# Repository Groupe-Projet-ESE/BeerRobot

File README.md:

# <div align="center">BeerRobot</div> 
__Last update of README__ : 23/01/2023

## Introduction
Elèves en option ESE (Electronique et Systèmes Embarqués) au sein de l'ENSEA (Ecole Nationale Supérieures de l'Electronique et de ses Applications), réalisant un robot comme projet central de leur option.  

## Objectifs du projet
Le but du projet est de créer un robot permettant d'attraper des canettes, de relever la couleur de cette dernière, se déplacer avec la canette attrapée et la déposer dans la zone adaptée selon sa couleur. Par ailleurs le robot devra se repérer sur une table afin de ne pas tomber.   

## Matériels et composants à notre disposition

__Microcontroleur__ : STM32G070RBT6 (Farnell : 3365377)  
__Quartz 16 MHz__ : (Farnell : 2853935)  
__Connecteur SWD/STLink__ : (Farnell : 3226055)  
__Driver moteur__ : ZXBM5210-S (Farnell : 3935372)   
__Moteurs__ : DfRobot FIT0520 ou FIT0521   
__Régulateur 5V__ : AZ1117CH2-5.0TRG1 (Farnell : 3942512)  
__Régulateur 3.3V__ : MIC5317-3.3YM5 (Farnell : 2920683)  
__Batterie NIMH 7.2V 1.3Ah__ (RS : 777-0377)    
__Capteur bordure__ : Sharp GP2Y0D805Z0F (Generationrobots : A-000000-00046)   
__Capteur TOF__ : VL53L0X (Generationrobots : A-000000-03233)   
__Capteur de couleur__ : VEML3328 (Farnell : 3517203)  
__Servomoteur__ : XL320 (Generationrobots : A-000000-01282)  
Connecteurs JST 2.54mm  

## Membres du groupe et rôles
Le groupe de projet est constitué de 4 membres, chacun ayant divers responsabilités.  
- __Chelsea COMLAN__ : responsable Hardware
- __Loïcia KOEHL__ : responsable intégration
- __Quentin SIMON__ : responsable Software
- __Alix HAVRET__ : responsable livrables

__Encadrants du projet__ : Mr Fiack , Mr Tauvel  
__Intervenants extérieur__ : Mme Quittel, Mr Jauffrey, Mr Le Bidan  

### Contenus des dossiers
La démonstration finale se trouve sur la master. 

#### Additional documents
Contient l'ensemble des images necessaire à la rédaction de ce README, le rapport de mi-projet rédigé en novembre ainsi que le diaporama de notre présentation du robot en décembre.   

  #### Hardware
Contient le projet Kicad avec l'ensemble des fichiers electronique ainsi que le fichier de routage du PCB.  
Le PCB a été produit à l'extérieur de l'ENSEA.  

  #### Software 
Contient les codes "annexes", c'est à dire les codes des composants testé sur le STM32F746NG.  
Le projet CubeIDE a destination de la STM32G0 (notre microcontroleur de projet) se trouve sur la master. 

  #### 3D 
  Contient certains fichiers 3D pour la réalisation du robot

## Architecture générale du projet

Au debut du projet nous avons eu la liste de l'ensemble des composants auxquels nous avions accès pour la réalisation du robot et afin de remplir ses divers fonctionnalités.   
Le schéma architectural au début du projet nous a permit de définir l'ensemble des entrées necessaires dans notre microcontroleur et les divers flux de données qui allaient entrer en jeu.  

### Rôles et utilité des divers composants, capteurs 
#### Moteurs FIT501
Deux Moteurs à courant continu, alimenté en xx V, permettant de faire tourner 2 roues. Le moteur a également un encodeur.  

### Servomoteur XL320
Servomoteur qui permettra de faire bouger la pince necessaire pour saisir les canettes.

### Capteur couleur TCS3200
Capteur permettant de detecter la couleur de la canette à l'aide de filtres superposés à des LEDS.

### Capteur de bordure 
Capteur infra-rouge qui détecte si il y a un object en face de lui.

### Capteur TOF 
Time Of Flight, renvoie le temps qu'a prit la source lumineuse du capteur pour rebondir sur un object et revenir. Cela nous permet d'avoir notre distance par rapport à un objet. (en mm)

## 3D du robot 
Nous avons prit la décision de modifier le design initial du robot sur onshape.  
Ajout d'un roulement en plus à l'avant, modification de l'emplacement de la pince et la forme de celle ci. Une fois le PCB reçu, des modifications ont été effectuées afin de permettre un bon placement de l'ensemble des fils.  
Par ailleurs nous avons aménagés divers emplacements pour les différents capteurs : couleurs, bordure et distance. 

## Hardware 
### Schema electrique
A partir du schema architectural réalisé au début du projet, nous avons commencé le schéma électrique du projet sur Kicad.  
Ce dernier a été séparé en plusieurs feuilles afin de pouvoir organiser les différentes partie : STM32, alimentation, capteurs, moteurs, servomoteur.

### PCB
__09/11/2022__ Reception du PCB  
__Soudeurs__ : Loïcia et Chelsea  
L'ensemble des soudures ont été réalisées à la main, lee 25/11/2022  l'ensemble des composants étaient soudés sur la carte.   
Nous avons soudés les connecteurs au fur et à mesure de la réalisation des tests.

## Software

Le code sera utilisé dans diverses tâches (utilisation de FreeRTOS). Chaque état décrit dans le diagramme à états correspondra à une tâche.  
Une tâche pourra faire appel à de la donnée, ou en consommer. Dans chaque tâche nous feront appel à divers bouts de code permettant de démarrer un capteur, un moteur, un servo, etc ...  

Pour effectuer nos tests sur les capteurs, nous avons implémentés un shell. Chacun des capteurs ont été validé sur la STM32F746NG, et ensuite leur code était intégré à la STM32G0.
La shell nous a permit de faire une première démonstration. 

### Moteurs : 
Après les premiers tests, nous avons remarqué que pour une même commande vitesse, les 2 roues ne tournaient pas à la même vitesse, de ce fait le robot n'allait pas droit.  Afin de régler ce problème il était nécessaire de mettre en place un asservissement.
#### Asservissement 
Nous avons décidé de faire un correcteur PI (Proportionnel Intégral).  

**schéma**

Pour cela il nous fallait donc récupérer des informations venant du robot et du microcontroleur :  
-	Valeur vitesse demandée  pour les roues
-	Valeur vitesse réelle des 2 roues (les 2 étant différentes du à la qualité des moteurs)  
-	Nombre de tick moteur  

Ces infos nous permettaient alors de créer le correcteur PI avec :  
-	Coefficient proportionnel Kp  
-	Coefficient intégrateur Ki  

Une fois avoir réussi à récupérer la valeur de la vitesse en entrée et le nombre de tick nous avons pu commencer à coder l’asservissement.  

Pour ce faire il fallait que l’on fasse la différence de valeur entre la valeur actuelle et la valeur précédente de vitesse. Par la suite, nous pouvions calculer l’erreur entre la valeur d’entrée et la vitesse du robot pour voir si il avançait à la vitesse souhaitée.  
Une fois toutes la valeurs et calculs mis en place, nous avons pu commencer la recherche des valeurs pour nos coefficients. Il fallait trouver les valeurs avec lesquelles il y avait le moins d’oscillation possible.  

### Fonctionnement des capteurs 
#### Capteur bordure 

#### Capteur TOF 
Le capteur TOF a un driver déja créé, ce qui nous a permit de réutiliser les fonctions déja existantes permettant l'initialisation du capteur, et la récupération des valeurs .L'activation de la pin GPIO nous permet d'acquérir les valeurs en continue tant que le TOF est actif.   
Lorsque que l'on veut utiliser 2 TOF, c'est la pin XSHUT qui rentre en jeux. Les 2 TOF étant sur le même I2C, on activera uniquement le TOF du capteur que l'on veut utiliser.  

#### Capteur couleurs
Non fonctionnel.

__Objectif de la présentation finale :__

La démo implémentée et téléchargée sur la master permet au robot de faire une première phase de démarrage, de se lancer en mode "recherche" canette. Une fois une canette repérée à une certaine distance, le robot continue sa recherche vers la zone où il a capté une canette. Une fois que la canette est captée dans le creue du robot, alors la pince est déclenchée en mode fermeture.

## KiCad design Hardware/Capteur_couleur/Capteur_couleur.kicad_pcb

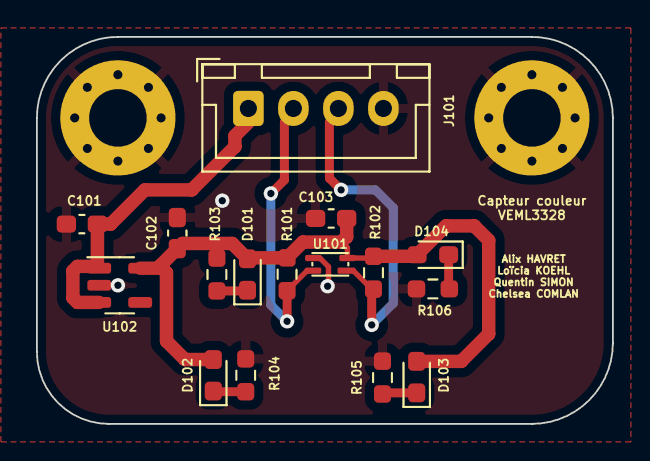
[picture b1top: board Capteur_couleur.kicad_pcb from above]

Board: 2 copper layers, 32.0 x 21.5 mm, 18 parts (0 on the bottom side), 9 nets.

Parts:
C101, C102: 1uF; C_0603_1608Metric_Pad1.08x0.95mm_HandSolder
C103: 100n; C_0603_1608Metric_Pad1.08x0.95mm_HandSolder
D101, D102, D103, D104: LED; LED_0603_1608Metric_Pad1.05x0.95mm_HandSolder
H101, H102: MountingHole_Pad; MountingHole_3.2mm_M3_Pad_Via
J101: JST_Couleur_3V; JST_XH_B4B-XH-A_1x04_P2.50mm_Vertical
R101, R102: 2.2k; R_0603_1608Metric_Pad0.98x0.95mm_HandSolder
R103, R104, R105, R106: WHITE; R_0603_1608Metric_Pad0.98x0.95mm_HandSolder
U101: VEML3328
U102: MCP1802x-xx02xOT; SOT-23-5

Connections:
+3.3V: C102.1, C103.1, D101.2 (A), D102.2 (A), D103.2 (A), D104.2 (A), R101.1, R102.1, R103.2, U101.4 (VDD), U102.5 (VOUT)
+5V: C101.1, J101.1, U102.1 (VIN), U102.3 (~SHDN)
GND: C101.2, C102.2, C103.2, H101.1, H102.1, J101.4, R104.2, R105.2, R106.2, U101.1 (GND), U102.2 (GND)
unnamed: D101.1 (K), R103.1
unnamed: D102.1 (K), R104.1
unnamed: D103.1 (K), R105.1
unnamed: D104.1 (K), R106.1
SCL: J101.3, R102.2, U101.3 (SCL)
SDA: J101.2, R101.2, U101.2 (SDA)

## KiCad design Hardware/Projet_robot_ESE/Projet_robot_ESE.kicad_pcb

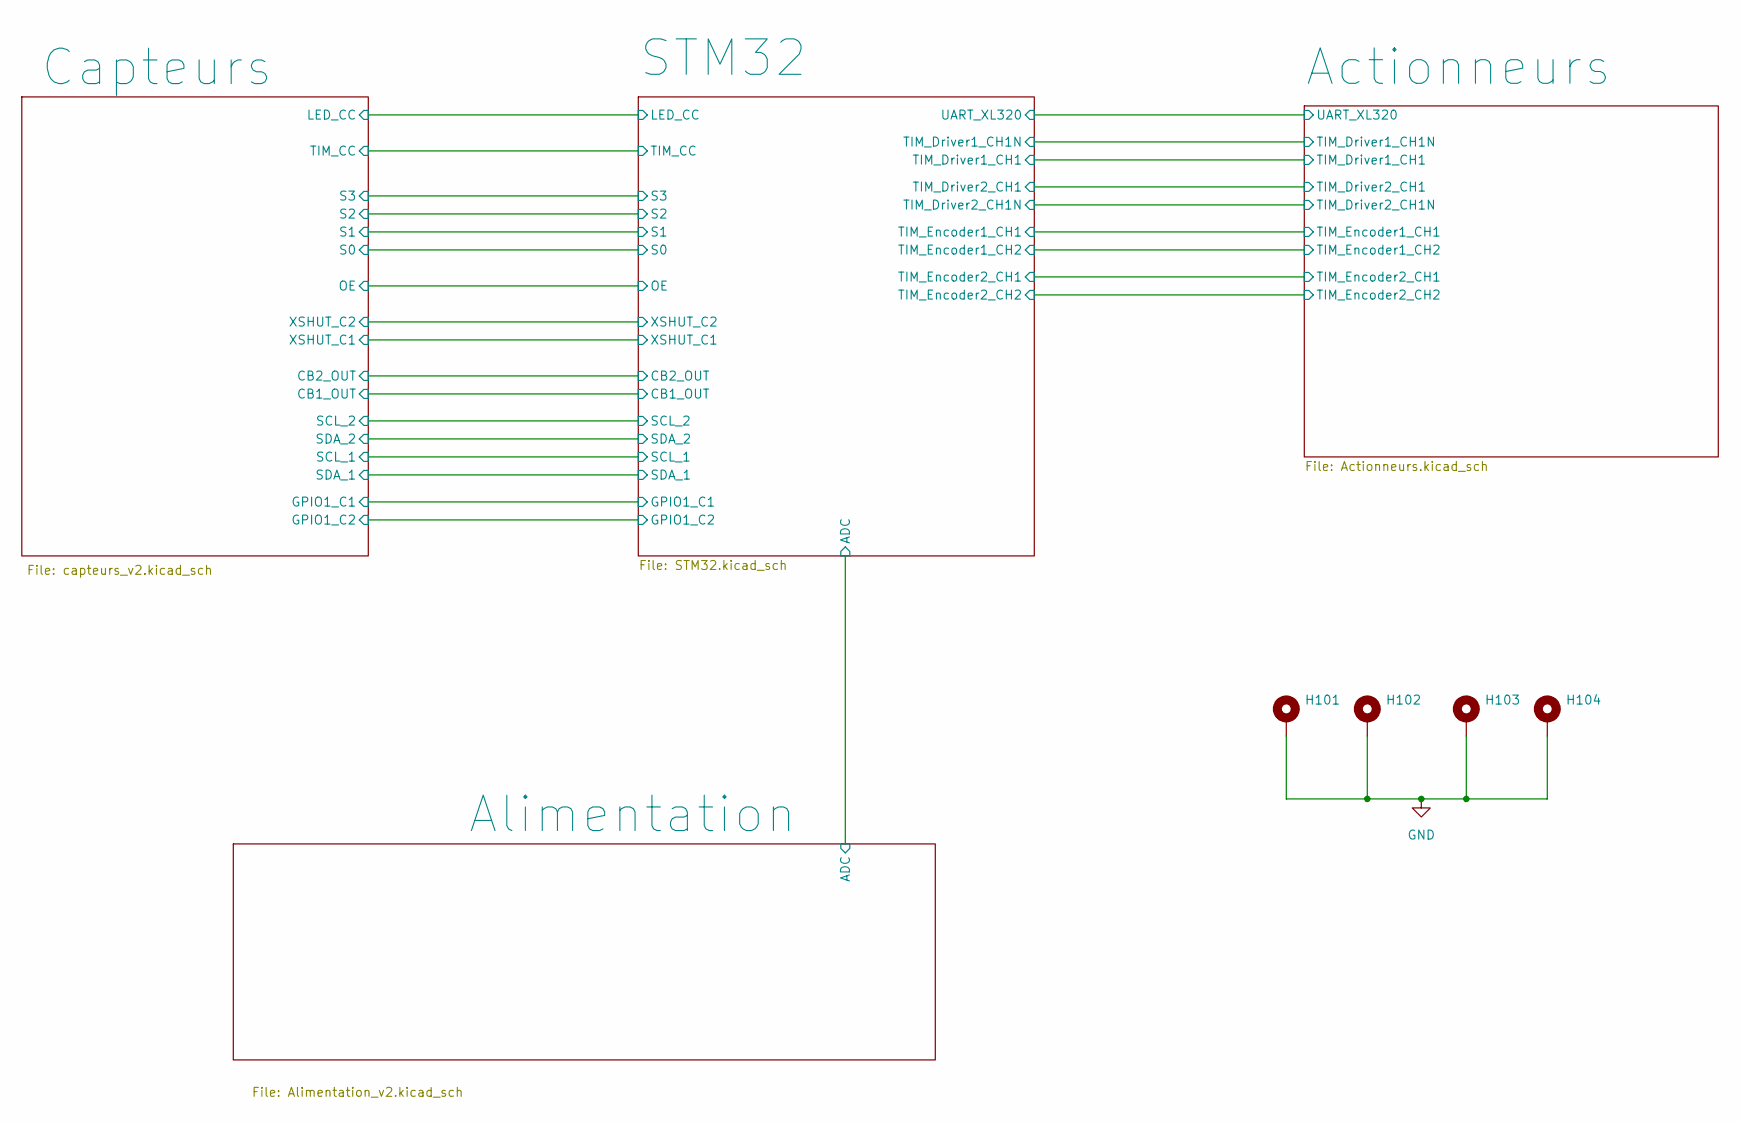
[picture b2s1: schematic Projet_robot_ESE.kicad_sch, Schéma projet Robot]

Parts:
H101, H102, H103, H104: MountingHole_Pad; MountingHole_3.2mm_M3_Pad_Via

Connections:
GND: H101.1, H102.1, H103.1, H104.1; also elsewhere on the board

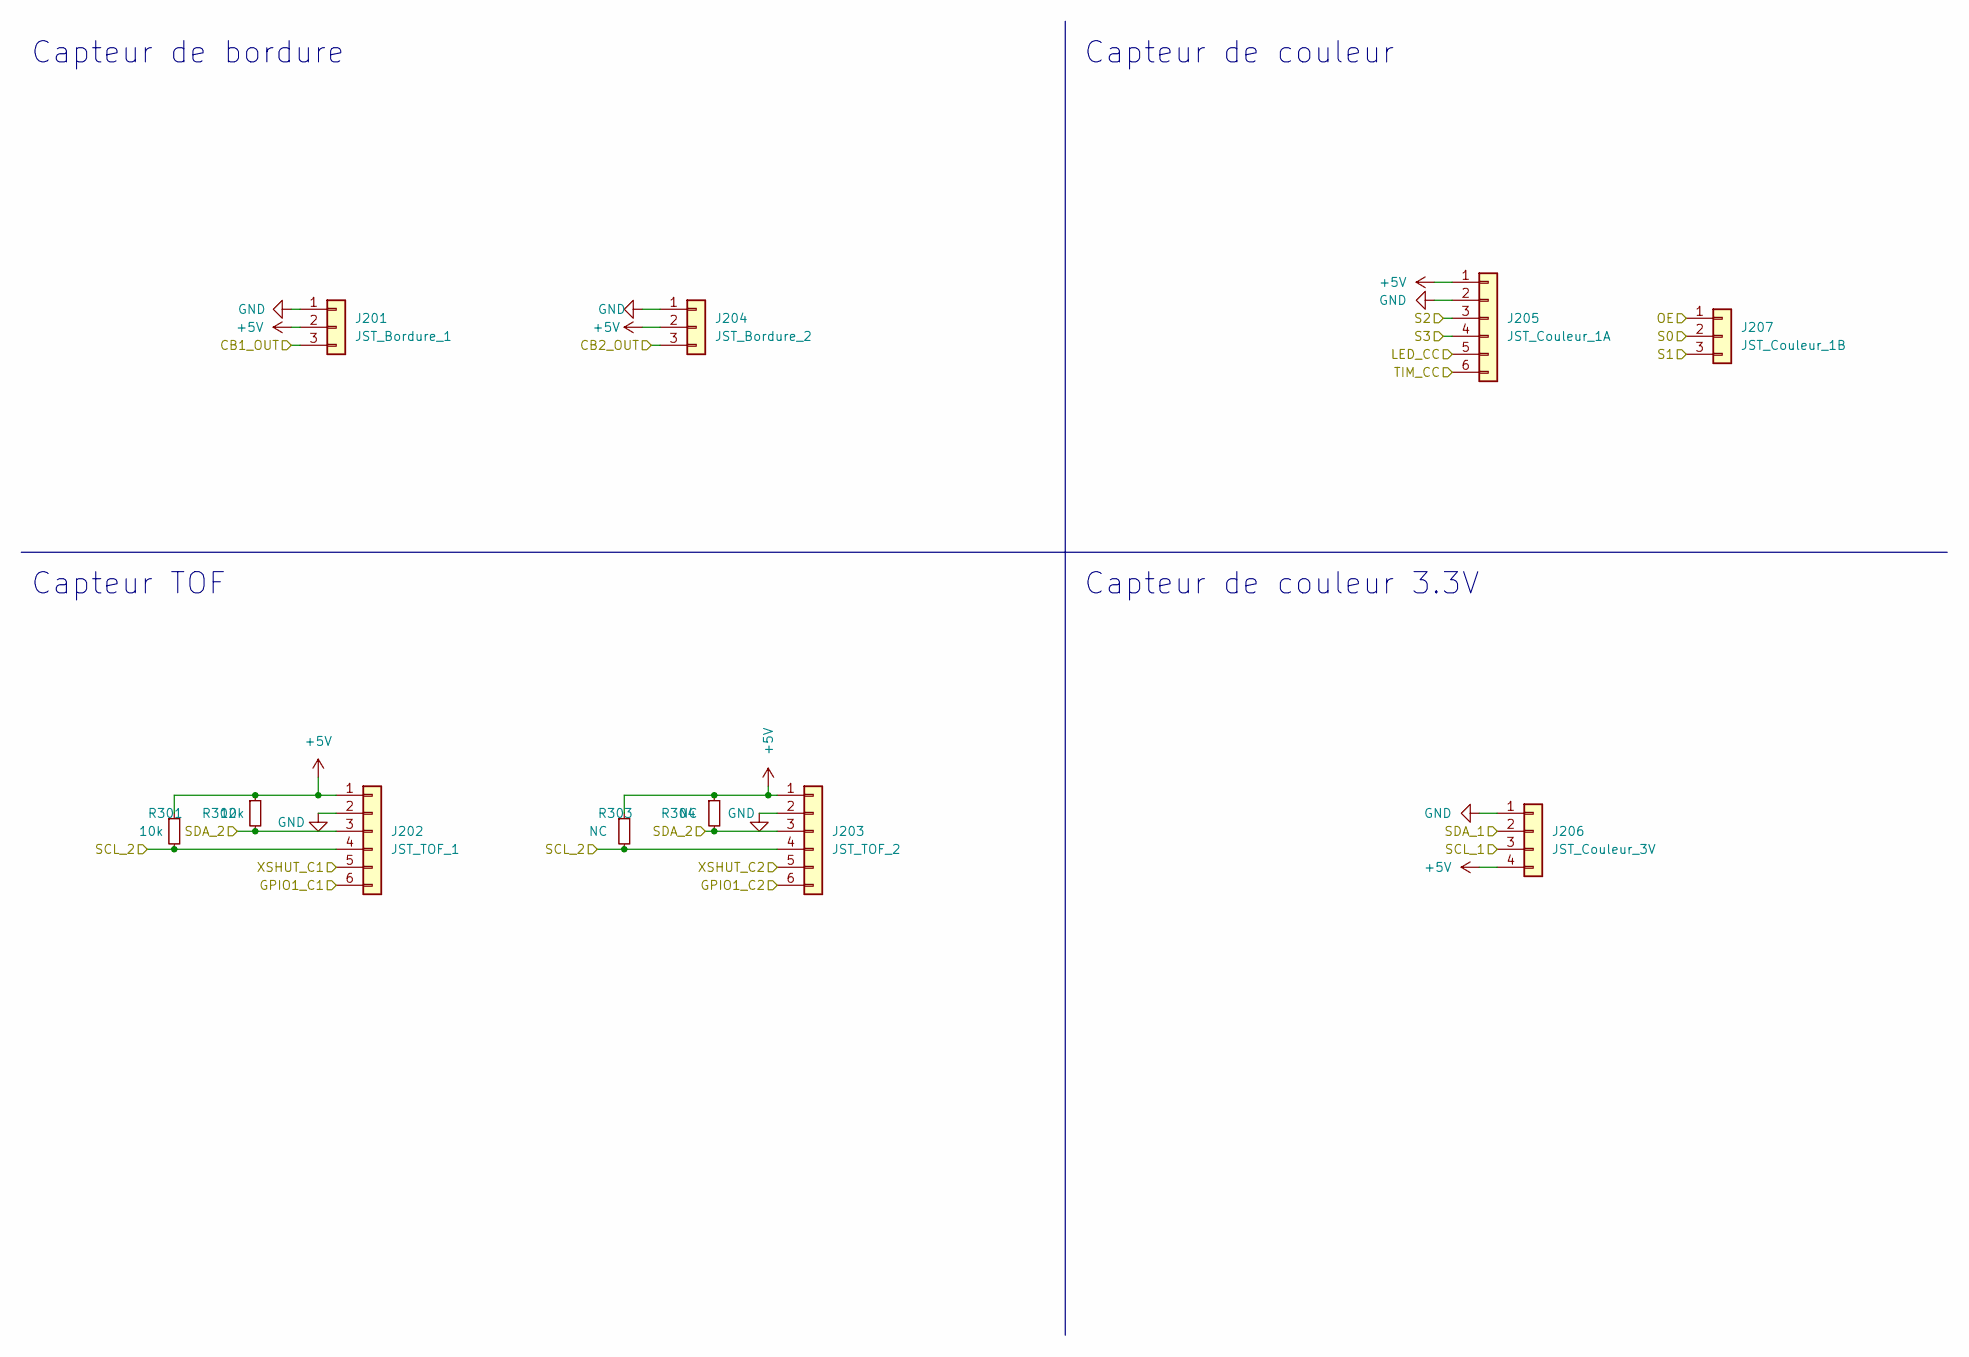
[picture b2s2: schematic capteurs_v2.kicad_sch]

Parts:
J201: JST_Bordure_1; JST_XH_B3B-XH-A_1x03_P2.50mm_Vertical
J202: JST_TOF_1; JST_XH_B6B-XH-A_1x06_P2.50mm_Vertical
J203: JST_TOF_2; JST_XH_B6B-XH-A_1x06_P2.50mm_Vertical
J204: JST_Bordure_2; JST_XH_B3B-XH-A_1x03_P2.50mm_Vertical
J205: JST_Couleur_1A; JST_XH_B6B-XH-A_1x06_P2.50mm_Vertical
J206: JST_Couleur_3V; JST_XH_B4B-XH-A_1x04_P2.50mm_Vertical
J207: JST_Couleur_1B; JST_XH_B3B-XH-A_1x03_P2.50mm_Vertical
R301, R302: 10k; R_0603_1608Metric_Pad0.98x0.95mm_HandSolder
R303, R304: NC; R_0603_1608Metric_Pad0.98x0.95mm_HandSolder

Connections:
+5V: J201.2, J202.1, J203.1, J204.2, J205.1, J206.4, R301.1, R302.1, R303.1, R304.1; also elsewhere on the board
/Capteurs/CB1_OUT: J201.3; also elsewhere on the board
/Capteurs/CB2_OUT: J204.3; also elsewhere on the board
/Capteurs/GPIO1_C1: J202.6; also elsewhere on the board
/Capteurs/GPIO1_C2: J203.6; also elsewhere on the board
/Capteurs/LED_CC: J205.5; also elsewhere on the board
/Capteurs/OE: J207.1; also elsewhere on the board
/Capteurs/S0: J207.2; also elsewhere on the board
/Capteurs/S1: J207.3; also elsewhere on the board
/Capteurs/S2: J205.3; also elsewhere on the board
/Capteurs/S3: J205.4; also elsewhere on the board
/Capteurs/SCL_1: J206.3; also elsewhere on the board
/Capteurs/SCL_2: J202.4, J203.4, R301.2, R303.2; also elsewhere on the board
/Capteurs/SDA_1: J206.2; also elsewhere on the board
/Capteurs/SDA_2: J202.3, J203.3, R302.2, R304.2; also elsewhere on the board
/Capteurs/TIM_CC: J205.6; also elsewhere on the board
/Capteurs/XSHUT_C1: J202.5; also elsewhere on the board
/Capteurs/XSHUT_C2: J203.5; also elsewhere on the board
GND: J201.1, J202.2, J203.2, J204.1, J205.2, J206.1; also elsewhere on the board

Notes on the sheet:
Capteur de couleur
Capteur TOF
Capteur de couleur 3.3V
Capteur de bordure

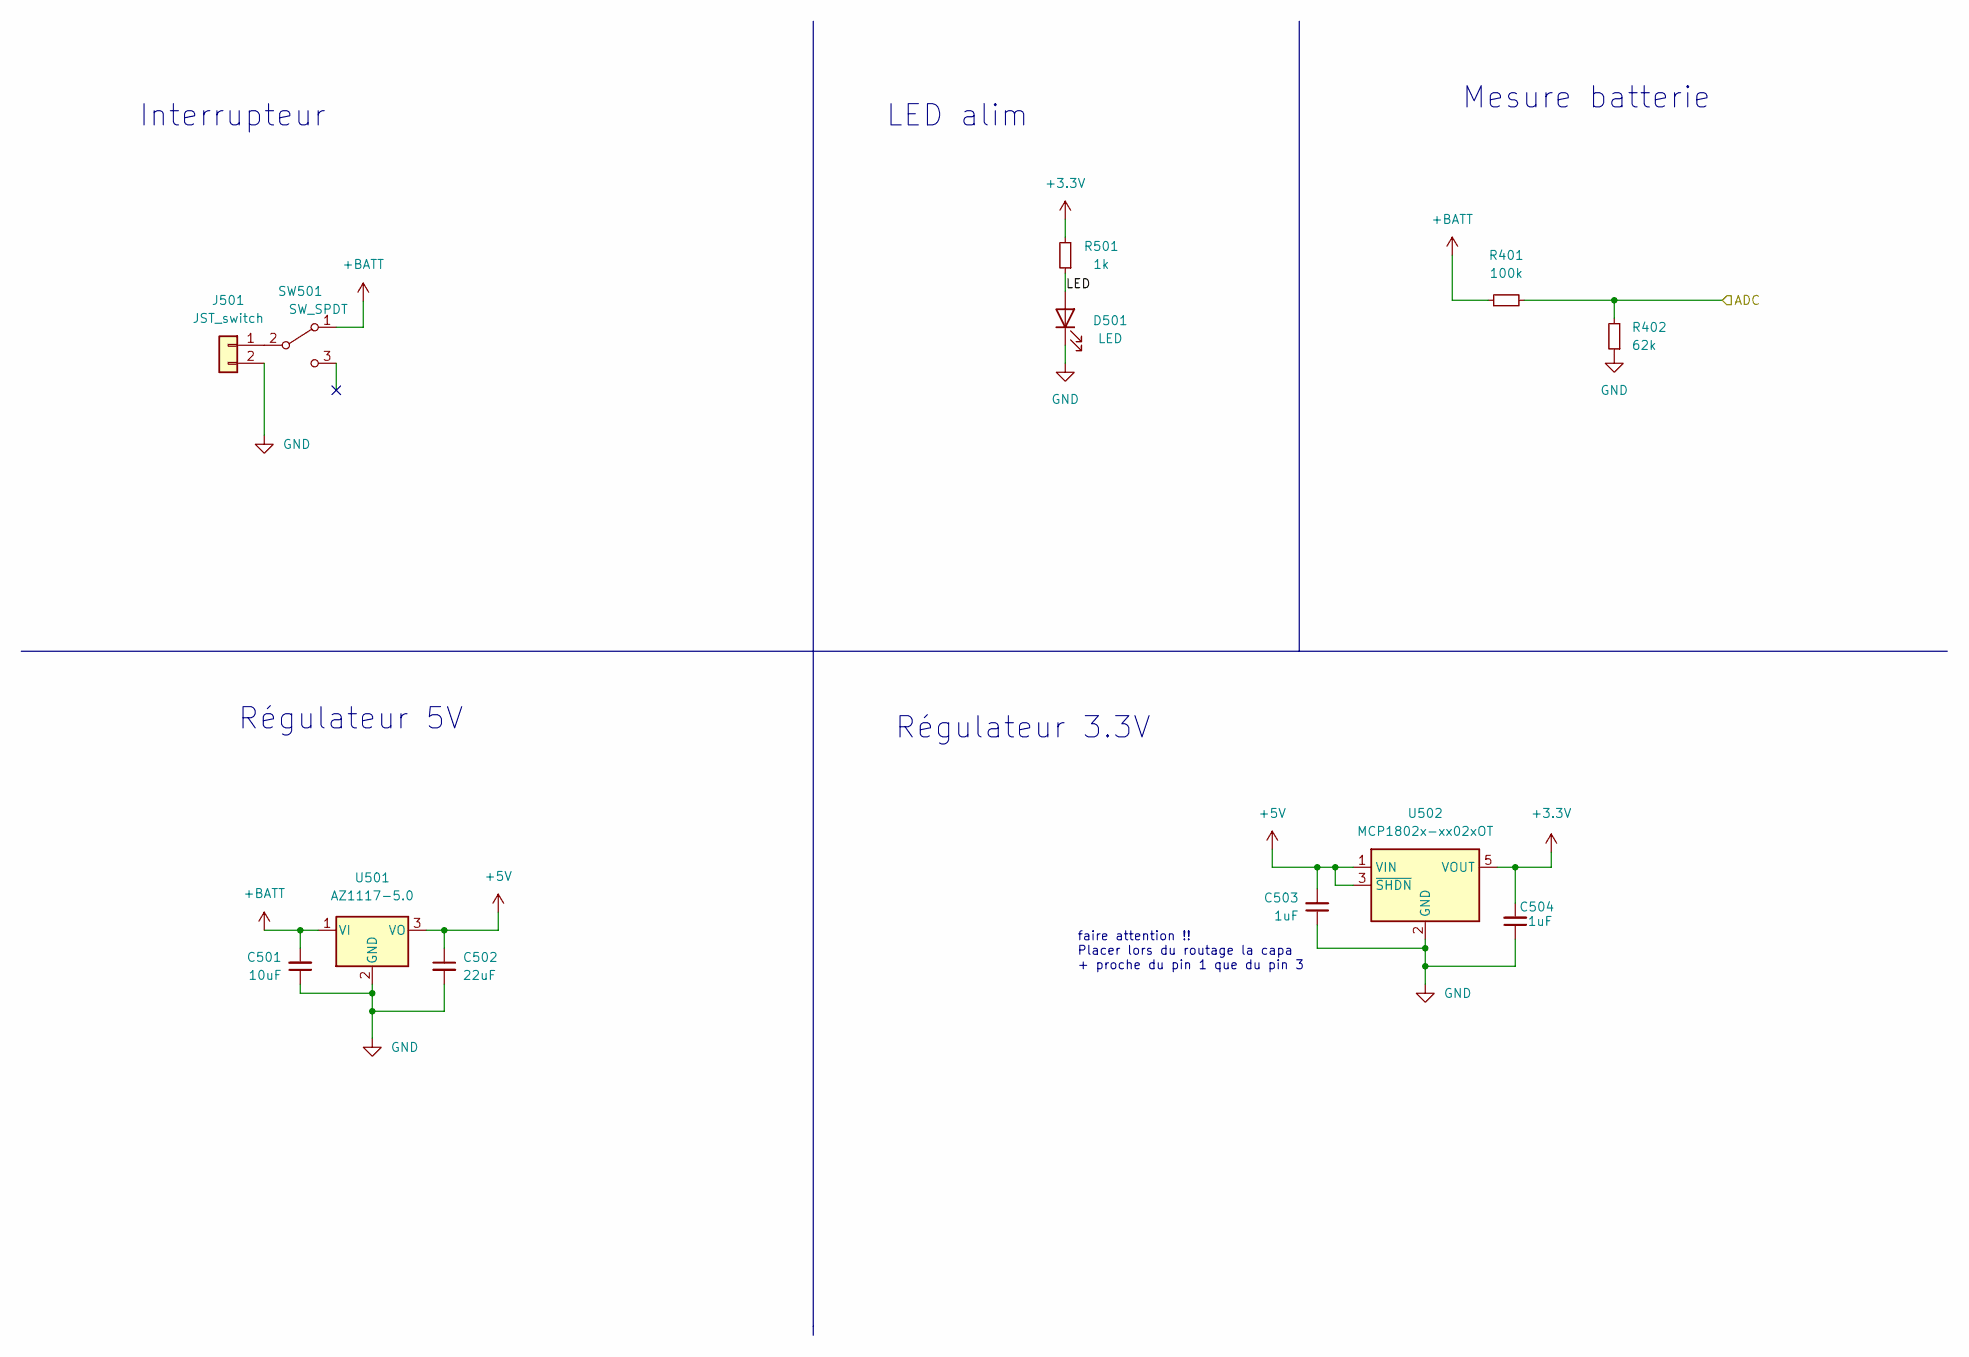
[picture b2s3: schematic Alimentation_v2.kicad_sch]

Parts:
C501: 10uF; C_0603_1608Metric_Pad1.08x0.95mm_HandSolder
C502: 22uF; C_0603_1608Metric_Pad1.08x0.95mm_HandSolder
C503, C504: 1uF; C_0603_1608Metric_Pad1.08x0.95mm_HandSolder
D501: LED; LED_0603_1608Metric_Pad1.05x0.95mm_HandSolder
J501: JST_switch; JST_XH_B2B-XH-A_1x02_P2.50mm_Vertical
R401: 100k; R_0603_1608Metric_Pad0.98x0.95mm_HandSolder
R402: 62k; R_0603_1608Metric_Pad0.98x0.95mm_HandSolder
R501: 1k; R_0603_1608Metric_Pad0.98x0.95mm_HandSolder
SW501: SW_SPDT; switch_pcb_robot
U501: AZ1117-5.0; SOT-223-3_TabPin2
U502: MCP1802x-xx02xOT; SOT-23-5

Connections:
+3.3V: C504.2, R501.2, U502.5 (VOUT); also elsewhere on the board
+5V: C502.1, C503.2, U501.3 (VO), U502.1 (VIN), U502.3 (~SHDN); also elsewhere on the board
+BATT: C501.2, R401.1, SW501.1 (A), U501.1 (VI); also elsewhere on the board
/Alimentation/ADC: R401.2, R402.2; also elsewhere on the board
/Alimentation/LED: D501.2 (A), R501.1
GND: C501.1, C502.2, C503.1, C504.1, D501.1 (K), J501.2, R402.1, U501.2 (GND), U502.2 (GND); also elsewhere on the board
unnamed: J501.1, SW501.2 (B)

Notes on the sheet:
Interrupteur
Régulateur 5V
LED alim
faire attention !! Placer lors du routage la capa + proche du pin 1 que du pin 3
Mesure batterie
Régulateur 3.3V

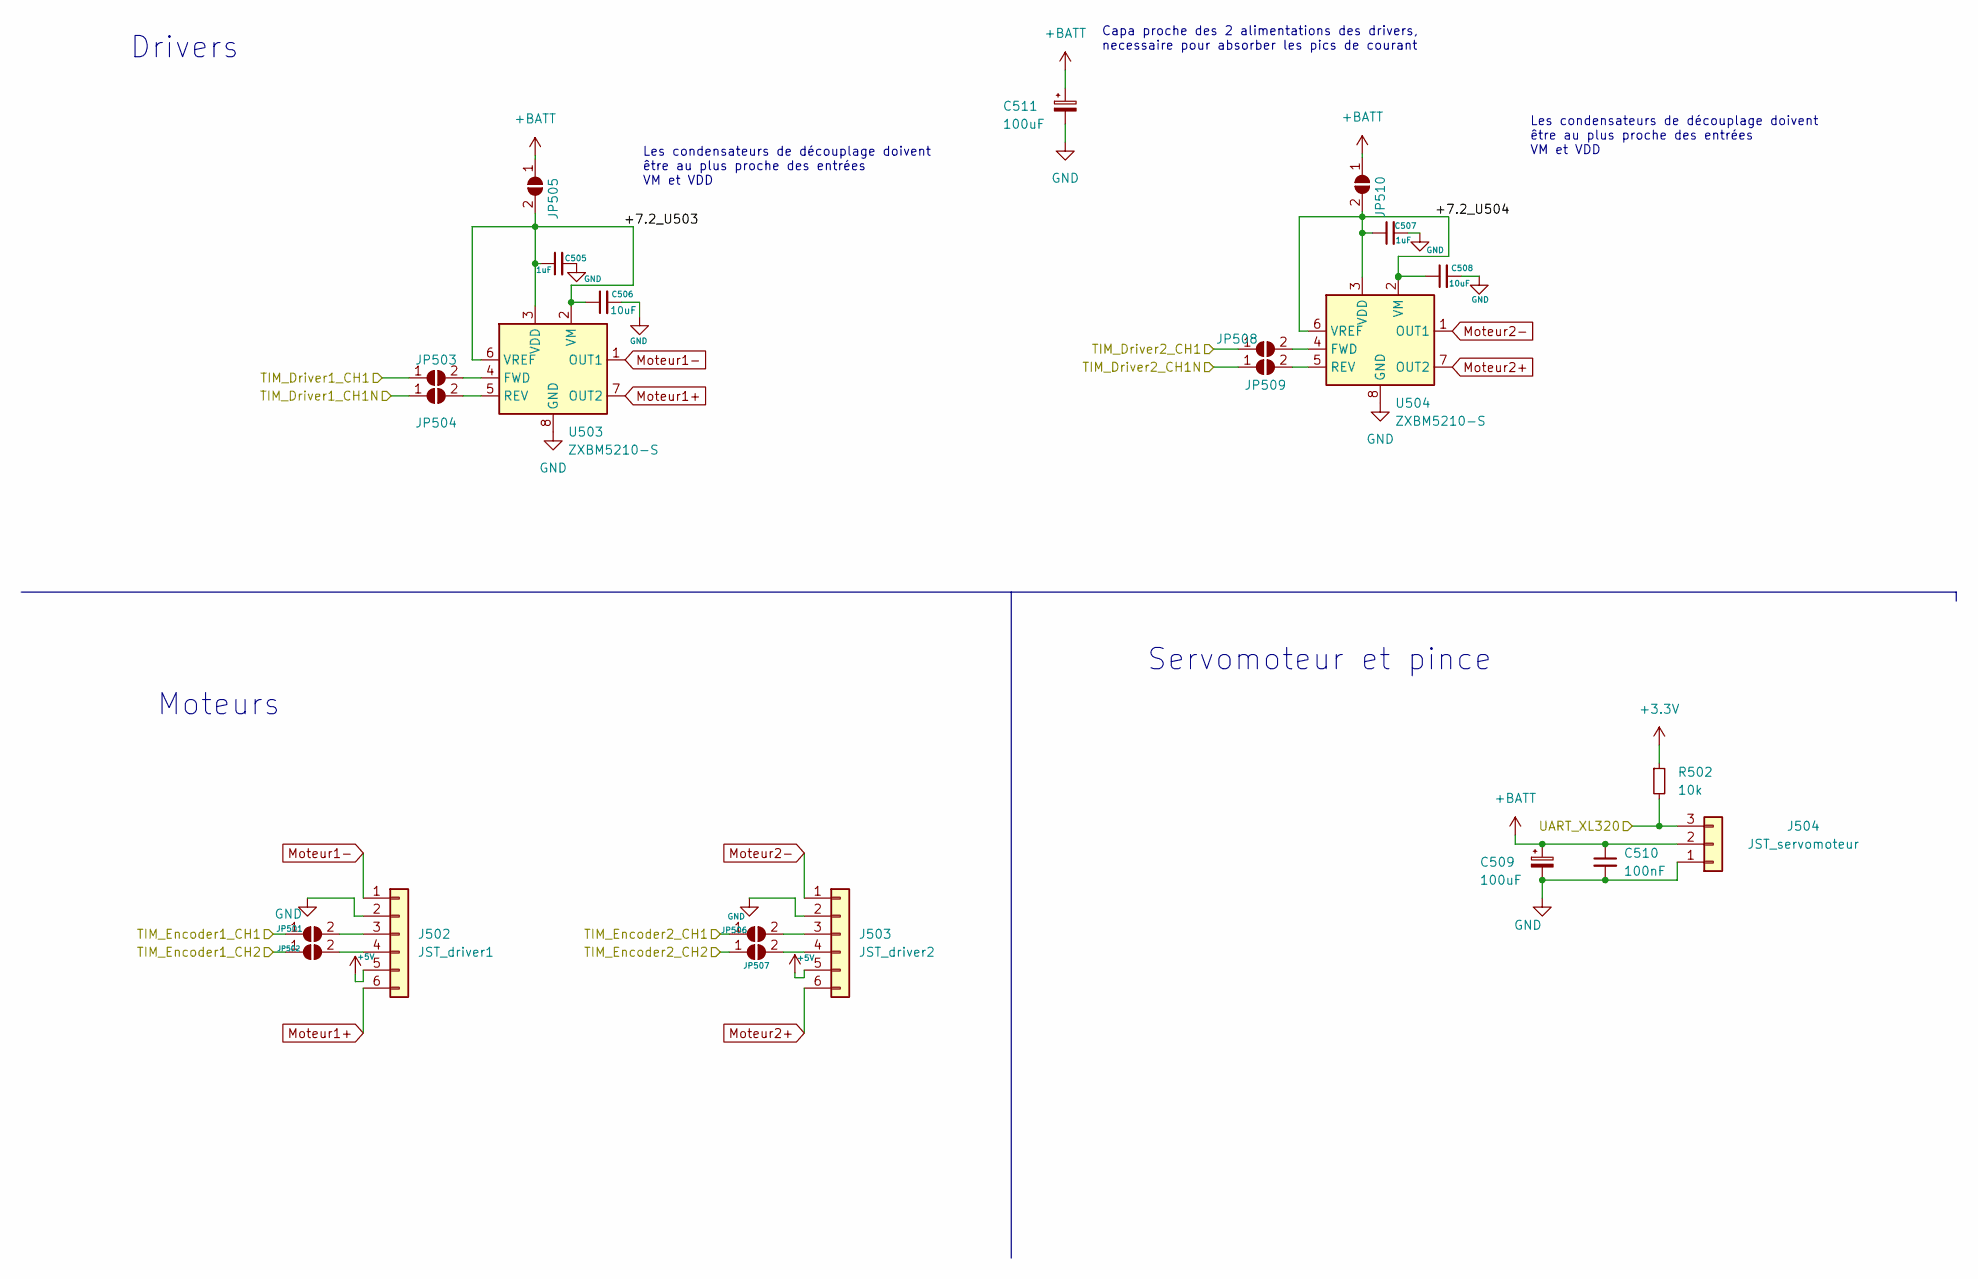
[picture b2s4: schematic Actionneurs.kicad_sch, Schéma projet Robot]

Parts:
C505, C507: 1uF; C_0603_1608Metric_Pad1.08x0.95mm_HandSolder
C506, C508: 10uF; C_0603_1608Metric_Pad1.08x0.95mm_HandSolder
C509, C511: 100uF; CP_Radial_D6.3mm_P2.50mm
C510: 100nF; C_0603_1608Metric_Pad1.08x0.95mm_HandSolder
J502: JST_driver1; JST_XH_B6B-XH-A_1x06_P2.50mm_Vertical
J503: JST_driver2; JST_XH_B6B-XH-A_1x06_P2.50mm_Vertical
J504: JST_servomoteur; JST_XH_B3B-XH-A_1x03_P2.50mm_Vertical
JP501, JP502, JP503, JP504, JP505, JP506, JP507, JP508, JP509, JP510: SolderJumper_2_Open; SolderJumper-2_P1.3mm_Open_TrianglePad1.0x1.5mm
R502: 10k; R_0603_1608Metric_Pad0.98x0.95mm_HandSolder
U503, U504: ZXBM5210-S; SOIC-8_3.9x4.9mm_P1.27mm

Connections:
+3.3V: R502.1; also elsewhere on the board
+5V: J502.5, J503.5; also elsewhere on the board
+BATT: C509.1, C510.1, C511.1, J504.2, JP505.1 (A), JP510.1 (A); also elsewhere on the board
/Actionneurs/+7.2_U503: C505.1, C506.1, JP505.2 (B), U503.2 (VM), U503.3 (VDD), U503.6 (VREF)
/Actionneurs/+7.2_U504: C507.1, C508.1, JP510.2 (B), U504.2 (VM), U504.3 (VDD), U504.6 (VREF)
/Actionneurs/TIM_Driver1_CH1: JP503.1 (A); also elsewhere on the board
/Actionneurs/TIM_Driver1_CH1N: JP504.1 (A); also elsewhere on the board
/Actionneurs/TIM_Driver2_CH1: JP508.1 (A); also elsewhere on the board
/Actionneurs/TIM_Driver2_CH1N: JP509.1 (A); also elsewhere on the board
/Actionneurs/TIM_Encoder1_CH1: JP501.1 (A); also elsewhere on the board
/Actionneurs/TIM_Encoder1_CH2: JP502.1 (A); also elsewhere on the board
/Actionneurs/TIM_Encoder2_CH1: JP506.1 (A); also elsewhere on the board
/Actionneurs/TIM_Encoder2_CH2: JP507.1 (A); also elsewhere on the board
/Actionneurs/UART_XL320: J504.3, R502.2; also elsewhere on the board
GND: C505.2, C506.2, C507.2, C508.2, C509.2, C510.2, C511.2, J502.2, J503.2, J504.1, U503.8 (GND), U504.8 (GND); also elsewhere on the board
Moteur1+: J502.6, U503.7 (OUT2)
Moteur1-: J502.1, U503.1 (OUT1)
Moteur2+: J503.6, U504.7 (OUT2)
Moteur2-: J503.1, U504.1 (OUT1)
unnamed: J502.3, JP501.2 (B)
unnamed: J502.4, JP502.2 (B)
unnamed: J503.3, JP506.2 (B)
unnamed: J503.4, JP507.2 (B)
unnamed: JP503.2 (B), U503.4 (FWD)
unnamed: JP504.2 (B), U503.5 (REV)
unnamed: JP508.2 (B), U504.4 (FWD)
unnamed: JP509.2 (B), U504.5 (REV)

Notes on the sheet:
Les condensateurs de découplage doivent être au plus proche des entrées VM et VDD
Servomoteur et pince
Drivers
Moteurs
Capa proche des 2 alimentations des drivers, necessaire pour absorber les pics de courant

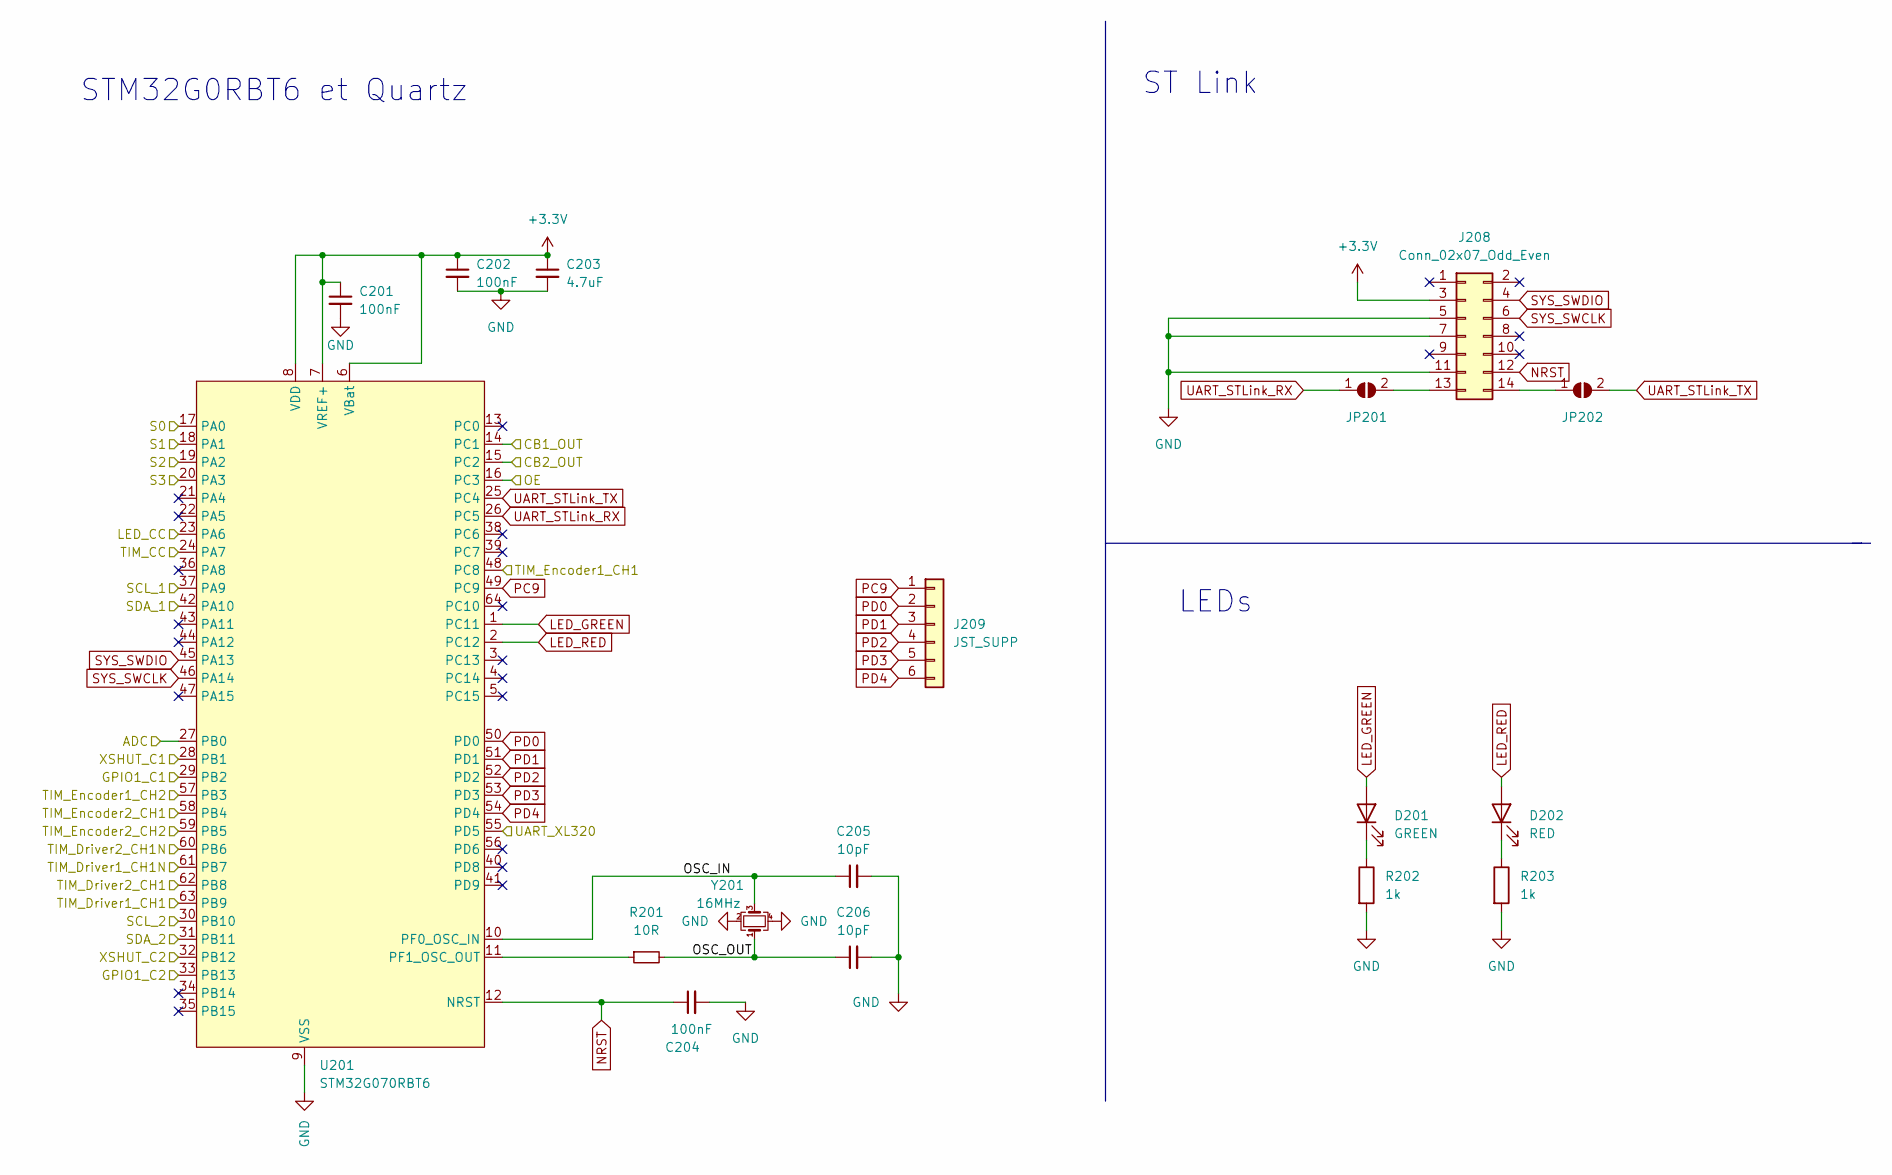
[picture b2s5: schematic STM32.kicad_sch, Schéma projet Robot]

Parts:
C201, C202, C204: 100nF; C_0603_1608Metric_Pad1.08x0.95mm_HandSolder
C203: 4.7uF; C_0603_1608Metric_Pad1.08x0.95mm_HandSolder
C205, C206: 10pF; C_0603_1608Metric_Pad1.08x0.95mm_HandSolder
D201: GREEN; LED_0603_1608Metric_Pad1.05x0.95mm_HandSolder
D202: RED; LED_0603_1608Metric_Pad1.05x0.95mm_HandSolder
J208: Conn_02x07_Odd_Even; PinHeader_2x07_P1.27mm_Vertical_SMD
J209: JST_SUPP; PinHeader_1x06_P2.54mm_Vertical
JP201, JP202: SolderJumper_2_Open; SolderJumper-2_P1.3mm_Open_TrianglePad1.0x1.5mm
R201: 10R; R_0603_1608Metric_Pad0.98x0.95mm_HandSolder
R202, R203: 1k; R_0603_1608Metric_Pad0.98x0.95mm_HandSolder
U201: STM32G070RBT6; LQFP-64_10x10mm_P0.5mm
Y201: 16MHz; Crystal_SMD_EuroQuartz_MT-4Pin_3.2x2.5mm

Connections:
+3.3V: C201.1, C202.1, C203.1, J208.3, U201.6 (VBat), U201.7 (VREF+), U201.8 (VDD); also elsewhere on the board
/Actionneurs/TIM_Driver1_CH1: U201.63 (PB9); also elsewhere on the board
/Actionneurs/TIM_Driver1_CH1N: U201.61 (PB7); also elsewhere on the board
/Actionneurs/TIM_Driver2_CH1: U201.62 (PB8); also elsewhere on the board
/Actionneurs/TIM_Driver2_CH1N: U201.60 (PB6); also elsewhere on the board
/Actionneurs/TIM_Encoder1_CH1: U201.48 (PC8); also elsewhere on the board
/Actionneurs/TIM_Encoder1_CH2: U201.57 (PB3); also elsewhere on the board
/Actionneurs/TIM_Encoder2_CH1: U201.58 (PB4); also elsewhere on the board
/Actionneurs/TIM_Encoder2_CH2: U201.59 (PB5); also elsewhere on the board
/Actionneurs/UART_XL320: U201.55 (PD5); also elsewhere on the board
/Alimentation/ADC: U201.27 (PB0); also elsewhere on the board
/Capteurs/CB1_OUT: U201.14 (PC1); also elsewhere on the board
/Capteurs/CB2_OUT: U201.15 (PC2); also elsewhere on the board
/Capteurs/GPIO1_C1: U201.29 (PB2); also elsewhere on the board
/Capteurs/GPIO1_C2: U201.33 (PB13); also elsewhere on the board
/Capteurs/LED_CC: U201.23 (PA6); also elsewhere on the board
/Capteurs/OE: U201.16 (PC3); also elsewhere on the board
/Capteurs/S0: U201.17 (PA0); also elsewhere on the board
/Capteurs/S1: U201.18 (PA1); also elsewhere on the board
/Capteurs/S2: U201.19 (PA2); also elsewhere on the board
/Capteurs/S3: U201.20 (PA3); also elsewhere on the board
/Capteurs/SCL_1: U201.37 (PA9); also elsewhere on the board
/Capteurs/SCL_2: U201.30 (PB10); also elsewhere on the board
/Capteurs/SDA_1: U201.42 (PA10); also elsewhere on the board
/Capteurs/SDA_2: U201.31 (PB11); also elsewhere on the board
/Capteurs/TIM_CC: U201.24 (PA7); also elsewhere on the board
/Capteurs/XSHUT_C1: U201.28 (PB1); also elsewhere on the board
/Capteurs/XSHUT_C2: U201.32 (PB12); also elsewhere on the board
/STM32/OSC_IN: C205.1, U201.10 (PF0_OSC_IN), Y201.3
/STM32/OSC_OUT: C206.1, R201.2, Y201.1
GND: C201.2, C202.2, C203.2, C204.2, C205.2, C206.2, J208.5, J208.7, J208.11, R202.2, R203.2, U201.9 (VSS), Y201.2, Y201.4; also elsewhere on the board
LED_GREEN: D201.2 (A), U201.1 (PC11)
LED_RED: D202.2 (A), U201.2 (PC12)
NRST: C204.1, J208.12, U201.12 (NRST)
unnamed: D201.1 (K), R202.1
unnamed: D202.1 (K), R203.1
unnamed: J208.13, JP201.2 (B)
unnamed: J208.14, JP202.1 (A)
unnamed: R201.1, U201.11 (PF1_OSC_OUT)
PC9: J209.1, U201.49 (PC9)
PD0: J209.2, U201.50 (PD0)
PD1: J209.3, U201.51 (PD1)
PD2: J209.4, U201.52 (PD2)
PD3: J209.5, U201.53 (PD3)
PD4: J209.6, U201.54 (PD4)
SYS_SWCLK: J208.6, U201.46 (PA14)
SYS_SWDIO: J208.4, U201.45 (PA13)
UART_STLink_RX: JP201.1 (A), U201.26 (PC5)
UART_STLink_TX: JP202.2 (B), U201.25 (PC4)

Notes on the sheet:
STM32G0RBT6 et Quartz
LEDs
ST Link

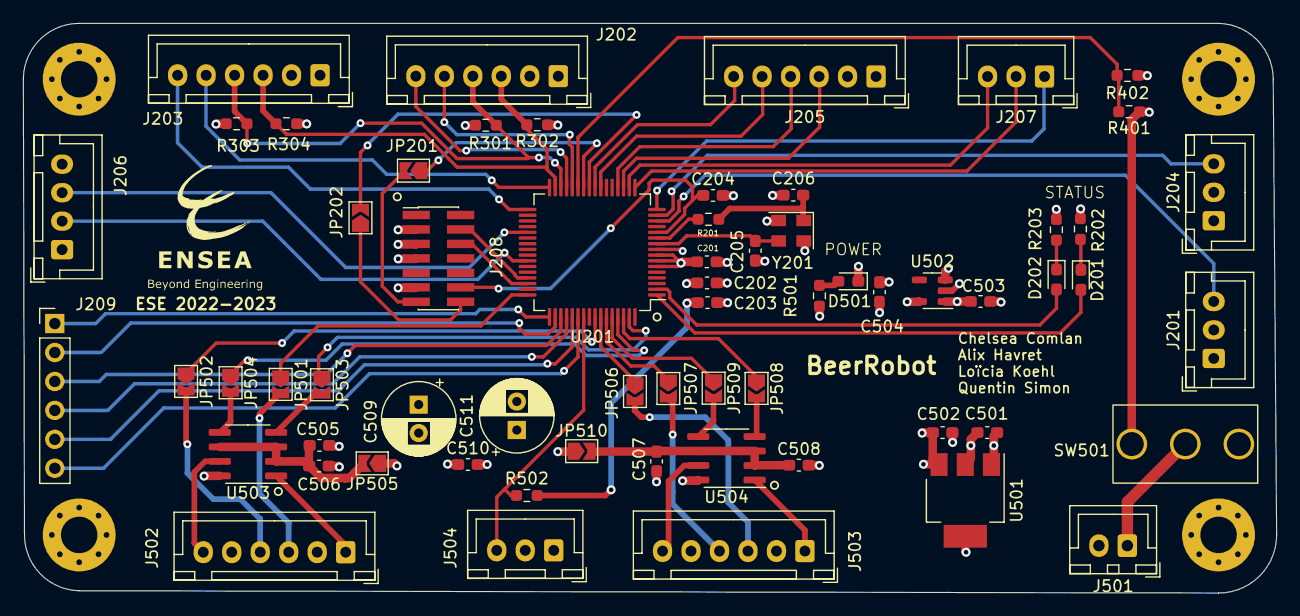
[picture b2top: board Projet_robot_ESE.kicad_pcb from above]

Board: 4 copper layers, 110.0 x 50.0 mm, 67 parts (0 on the bottom side), 67 nets.

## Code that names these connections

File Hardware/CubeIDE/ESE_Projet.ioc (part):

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Mcu.Name=STM32G070RBTx
Mcu.Package=LQFP64
Mcu.UserName=STM32G070RBTx
PA0.GPIOParameters=GPIO_Label
PA0.GPIO_Label=S0
PA0.Signal=GPIO_Output
PA1.GPIOParameters=GPIO_Label
PA1.GPIO_Label=S1
PA1.Signal=GPIO_Output
PA10.GPIOParameters=GPIO_Label
PA10.GPIO_Label=SDA_1
PA10.Mode=I2C
PA10.Signal=I2C1_SDA
PA13.Mode=Serial_Wire
PA13.Signal=SYS_SWDIO
PA14-BOOT0.Mode=Serial_Wire
PA14-BOOT0.Signal=SYS_SWCLK
PA2.GPIOParameters=GPIO_Label
PA2.GPIO_Label=S2
PA2.Signal=GPIO_Output
PA3.GPIOParameters=GPIO_Label
PA3.GPIO_Label=S3
PA3.Signal=GPIO_Output
PA6.GPIOParameters=GPIO_Label
PA6.GPIO_Label=LED_CC
PA6.Signal=GPIO_Output
PA7.GPIOParameters=GPIO_Label
PA7.GPIO_Label=TIM_CC
PA7.Signal=S_TIM14_CH1
PA9.GPIOParameters=GPIO_Label
PA9.GPIO_Label=SCL_1
PA9.Mode=I2C
PA9.Signal=I2C1_SCL
PB0.GPIOParameters=GPIO_Label
PB0.GPIO_Label=ADC
PB0.Mode=IN8
PB0.Signal=ADC1_IN8
PB1.GPIOParameters=GPIO_Label
PB1.GPIO_Label=XSHUT_C1
PB1.Signal=GPIO_Input
PB10.GPIOParameters=GPIO_Label
PB10.GPIO_Label=SCL_2
PB10.Mode=I2C
PB10.Signal=I2C2_SCL
PB11.GPIOParameters=GPIO_Label
PB11.GPIO_Label=SDA_2
PB11.Mode=I2C
PB11.Signal=I2C2_SDA
PB12.GPIOParameters=GPIO_Label
PB12.GPIO_Label=XSHUT_C2
PB12.Signal=GPIO_Input
PB13.GPIOParameters=GPIO_Label
PB13.GPIO_Label=GPIO1_C2
PB13.Signal=GPIO_Output
PB2.GPIOParameters=GPIO_Label
PB2.GPIO_Label=GPIO1_C1
PB2.Signal=GPIO_Output
PB3.GPIOParameters=GPIO_Label
PB3.GPIO_Label=TIM_Encoder1_CH2
PB3.Signal=S_TIM1_CH2
PB4.GPIOParameters=GPIO_Label
PB4.GPIO_Label=TIM_Encoder2_CH1
PB4.Signal=S_TIM3_CH1
PB5.GPIOParameters=GPIO_Label
PB5.GPIO_Label=TIM_Encoder2_CH2
PB5.Signal=S_TIM3_CH2
PB6.GPIOParameters=GPIO_Label
PB6.GPIO_Label=TIM_Driver2_CH1N
PB6.Mode=PWM Generation1 CH1 CH1N
PB6.Signal=TIM16_CH1N
PB7.GPIOParameters=GPIO_Label
PB7.GPIO_Label=TIM_Driver1_CH1N
PB7.Mode=PWM Generation1 CH1 CH1N
PB7.Signal=TIM17_CH1N
PB8.GPIOParameters=GPIO_Label
PB8.GPIO_Label=TIM_Driver2_CH1
PB8.Signal=S_TIM16_CH1
PB9.GPIOParameters=GPIO_Label
PB9.GPIO_Label=TIM_Driver1_CH1
PB9.Signal=S_TIM17_CH1
PC1.GPIOParameters=GPIO_Label
PC1.GPIO_Label=CB1_OUT
PC1.Signal=GPXTI1
PC11.GPIOParameters=GPIO_Label
PC11.GPIO_Label=LED_GREEN
PC11.Signal=GPIO_Output
PC12.GPIOParameters=GPIO_Label
PC12.GPIO_Label=LED_RED
PC12.Signal=GPIO_Output
PC2.GPIOParameters=GPIO_Label
PC2.GPIO_Label=CB2_OUT
PC2.Signal=GPXTI2
PC3.GPIOParameters=GPIO_Label
PC3.GPIO_Label=OE
PC3.Signal=GPIO_Output
PC4.GPIOParameters=GPIO_Label
PC4.GPIO_Label=UART_STLink_TX
PC4.Mode=Asynchronous
PC4.Signal=USART1_TX
PC5.GPIOParameters=GPIO_Label
PC5.GPIO_Label=UART_STLink_RX
PC5.Mode=Asynchronous
PC5.Signal=USART1_RX
PC8.GPIOParameters=GPIO_Label
PC8.GPIO_Label=TIM_Encoder1_CH1
PC8.Signal=S_TIM1_CH1
PD5.GPIOParameters=GPIO_Label
PD5.GPIO_Label=UART_XL320
PD5.Mode=Half_duplex(single_wire_mode)
PD5.Signal=USART2_TX
PF0-OSC_IN\ (PF0).Mode=HSE-External-Oscillator
PF0-OSC_IN\ (PF0).Signal=RCC_OSC_IN
PF1-OSC_OUT\ (PF1).Mode=HSE-External-Oscillator
PF1-OSC_OUT\ (PF1).Signal=RCC_OSC_OUT
RCC.HSE_VALUE=32000000
RCC.SYSCLKFreq_VALUE=64000000
RCC.SYSCLKSource=RCC_SYSCLKSOURCE_PLLCLK
board=custom
